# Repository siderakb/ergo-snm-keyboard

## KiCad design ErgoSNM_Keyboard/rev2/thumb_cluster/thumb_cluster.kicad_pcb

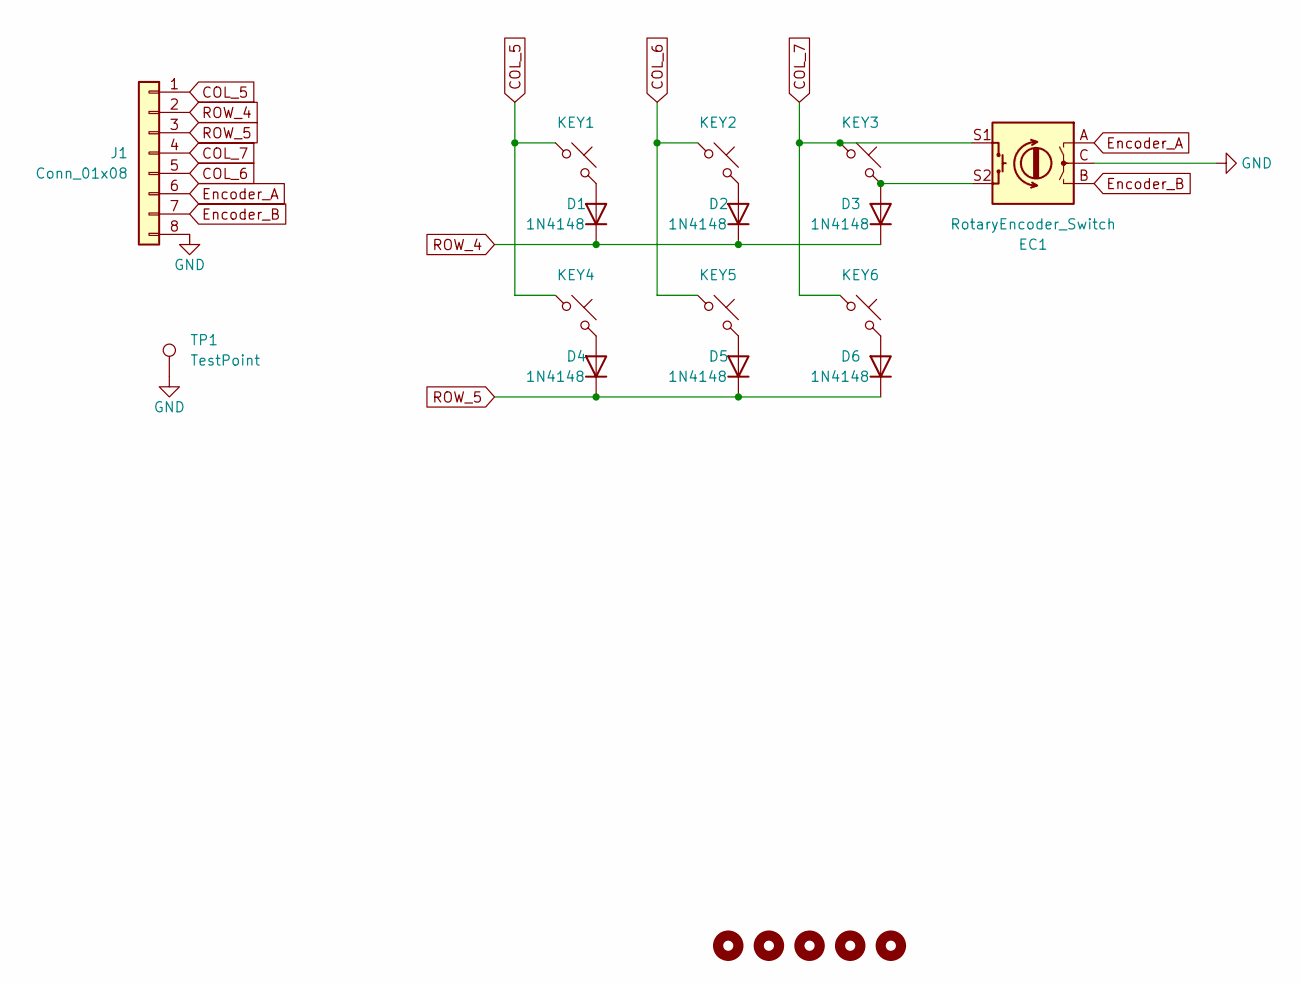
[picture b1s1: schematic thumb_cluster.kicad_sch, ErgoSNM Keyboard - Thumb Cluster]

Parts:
D1, D2, D3, D4, D5, D6: 1N4148; D_SOD-123; MFR. Part # 1N4148W; LCSC C81598
EC1: RotaryEncoder_Switch; RotaryEncoder_Alps_EC11E-Switch_Vertical_H20mm
H1, H2, H3, H4, H5: MountingHole; MountingHole_2.2mm_M2
J1: Conn_01x08; FPC_8P_0.5mm_AFC01-S08FCA-00; MFR. Part # SM08B-GHS-TB(LF)(SN); LCSC C265111
KEY1, KEY2, KEY3, KEY4, KEY5, KEY6: SW_Push_45deg; MX_switch_PTH_hotswap_A
TP1: TestPoint; TestPoint_Pad_D2.5mm

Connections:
COL_5: J1.1, KEY1.1, KEY4.1
COL_6: J1.5, KEY2.1, KEY5.1
COL_7: EC1.S1, J1.4, KEY3.1, KEY6.1
Encoder_A: EC1.A, J1.6
Encoder_B: EC1.B, J1.7
GND: EC1.C, J1.8, TP1.1
unnamed: D1.2 (A), KEY1.2
unnamed: D2.2 (A), KEY2.2
unnamed: D3.2 (A), EC1.S2, KEY3.2
unnamed: D4.2 (A), KEY4.2
unnamed: D5.2 (A), KEY5.2
unnamed: D6.2 (A), KEY6.2
ROW_4: D1.1 (K), D2.1 (K), D3.1 (K), J1.2
ROW_5: D4.1 (K), D5.1 (K), D6.1 (K), J1.3

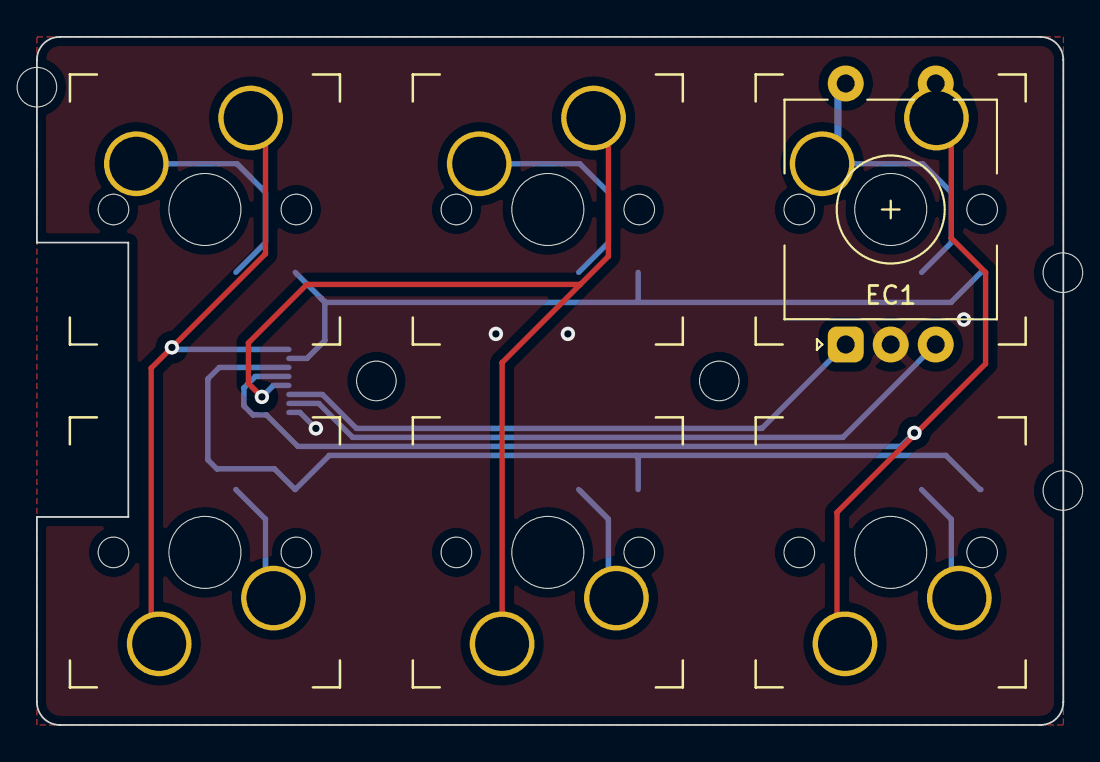
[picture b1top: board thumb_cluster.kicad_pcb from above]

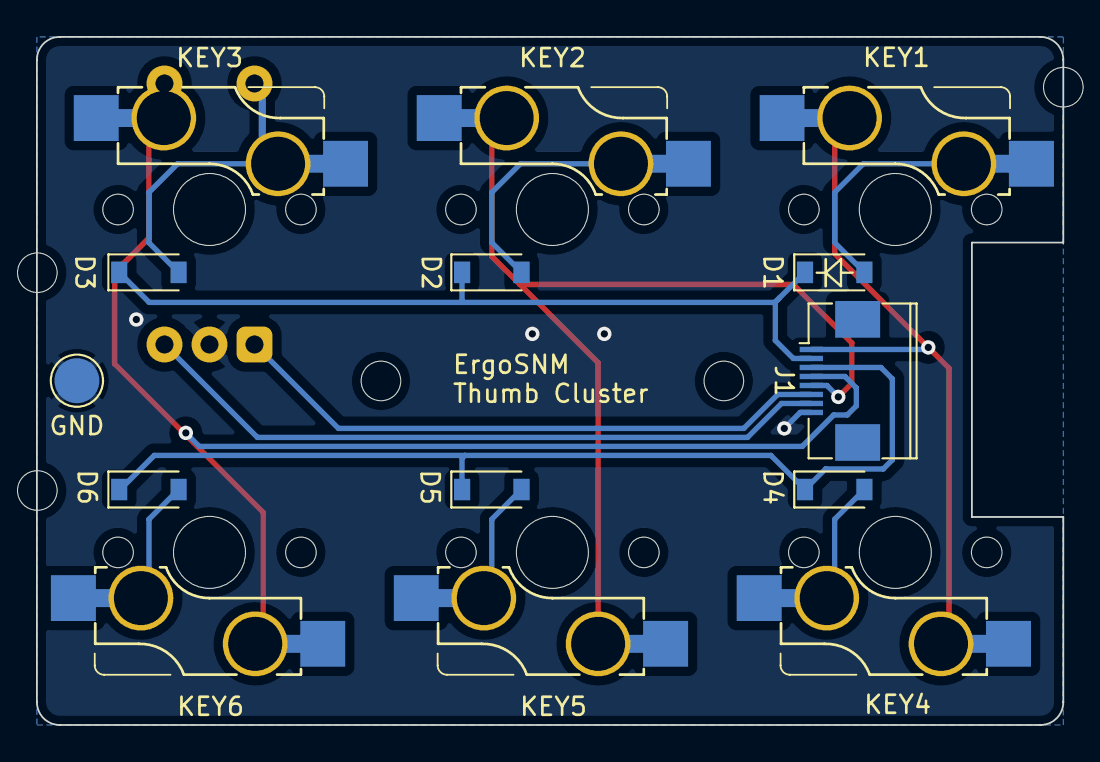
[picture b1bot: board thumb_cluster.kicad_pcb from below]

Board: 2 copper layers, 57.0 x 38.2 mm, 20 parts (8 on the bottom side), 14 nets.

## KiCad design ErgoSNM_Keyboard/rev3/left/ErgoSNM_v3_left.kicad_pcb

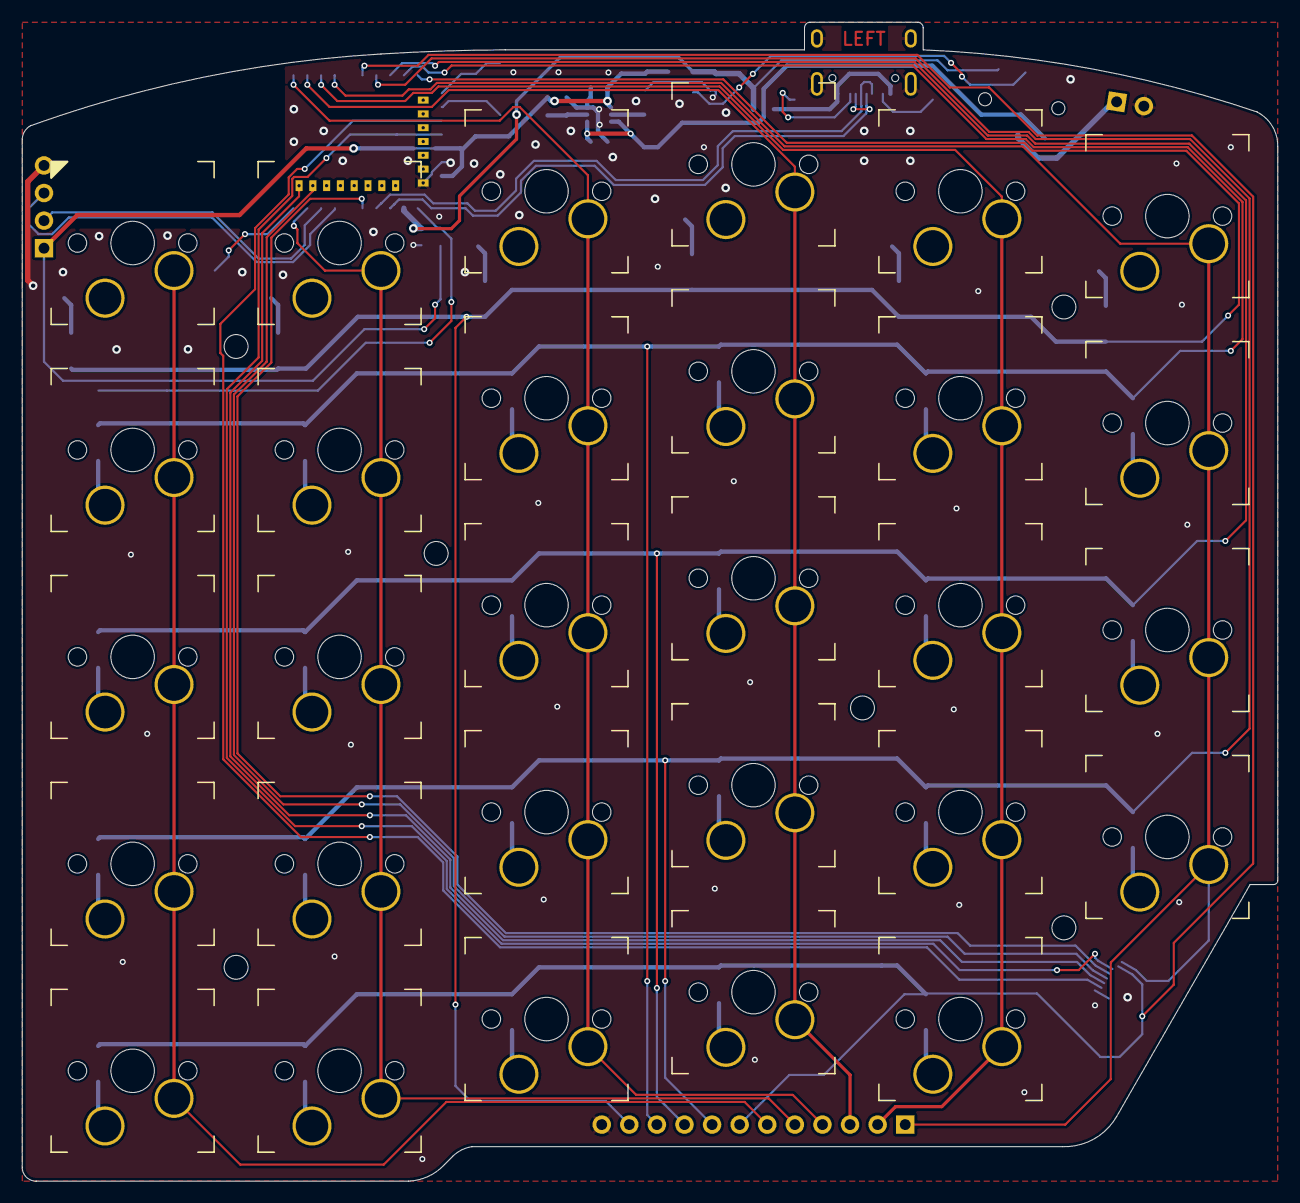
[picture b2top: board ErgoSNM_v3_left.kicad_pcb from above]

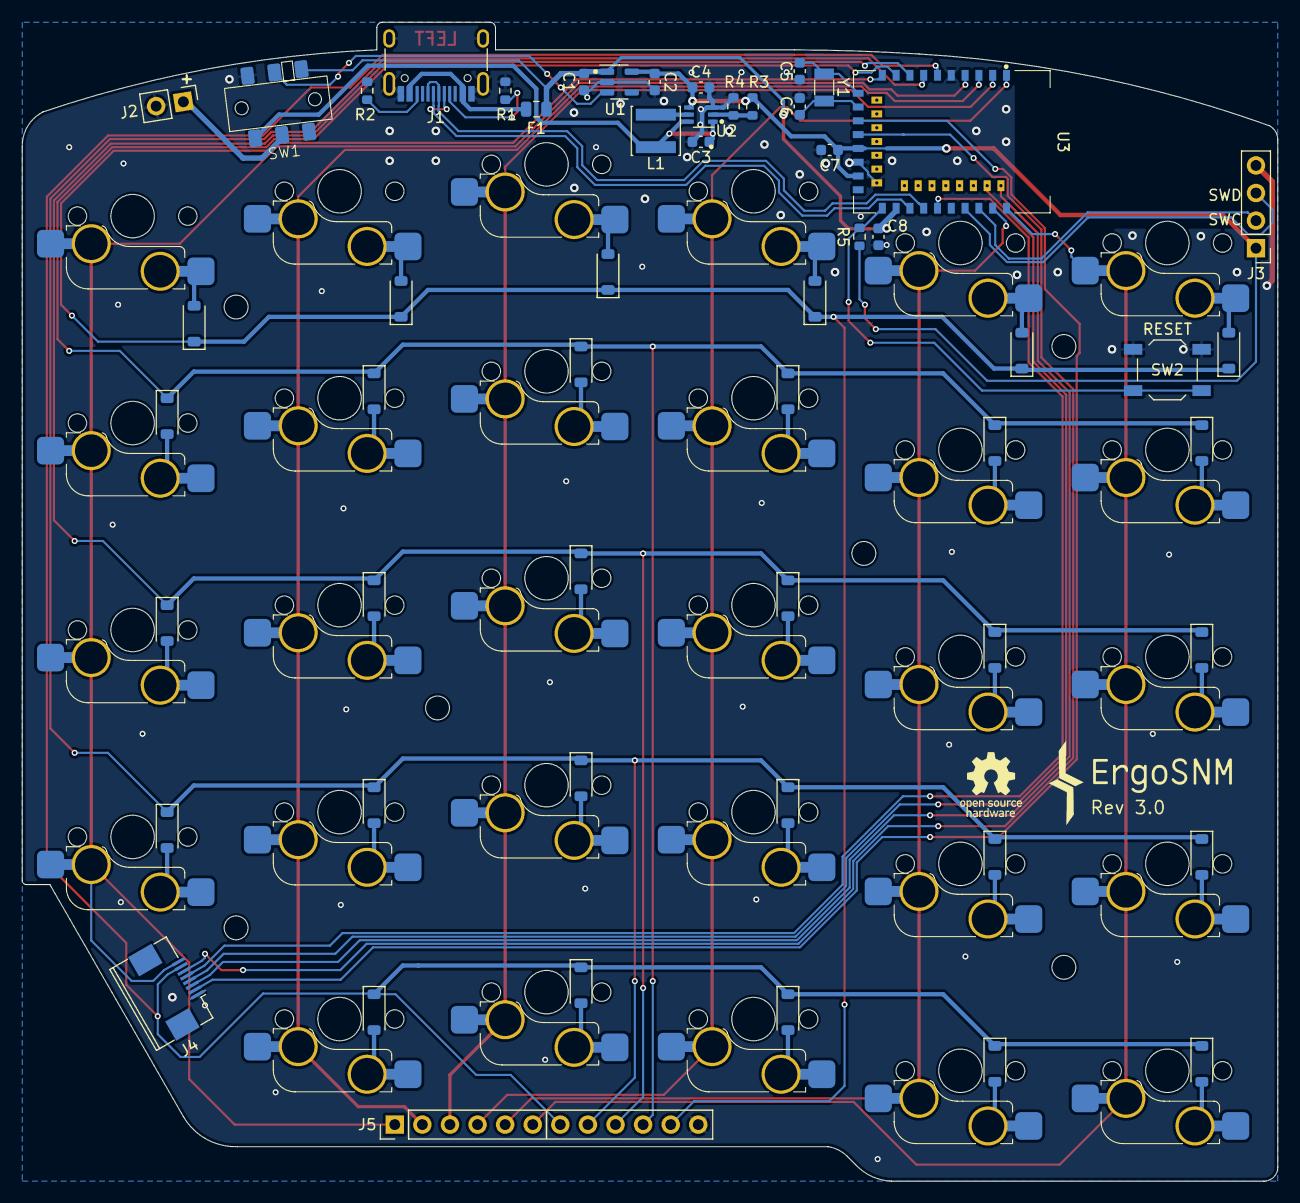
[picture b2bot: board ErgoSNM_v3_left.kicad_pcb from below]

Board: 2 copper layers, 115.6 x 106.7 mm, 90 parts (61 on the bottom side), 63 nets.

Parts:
C1, C2: 1uF; C_0603_1608Metric
C3, C4, C7, C8: 10uF; C_0603_1608Metric
C5, C6: 12pF; C_0603_1608Metric
D1, D2, D3, D4, D5, D6, D7, D8, D9, D10, D11, D12, D13, D14, D15, D16, D17, D18, D19, D20, D21, D22, D23, D24, D25, D26, D27, D28, D29: 1N4148; D_SOD-123
F1: 500mA, 6V; Fuse_0805_2012Metric
H1, H2, H3, H4, H5, H6: MountingHole; MountingHole_2.2mm_M2
J1: USB_C_Receptacle_USB2.0; USB_C_Receptacle_HRO_TYPE-C-31-M-12
J2: Conn_01x02; PinHeader_1x02_P2.54mm_Vertical
J3: Conn_01x04; PinHeader_1x04_P2.54mm_Vertical
J4: Conn_01x08; FPC_8P_0.5mm_AFC01-S08FCA-00
J5: Conn_01x12; PinHeader_1x12_P2.54mm_Vertical
KEY1, KEY2, KEY3, KEY4, KEY5, KEY6, KEY7, KEY8, KEY9, KEY10, KEY11, KEY12, KEY13, KEY14, KEY15, KEY16, KEY17, KEY18, KEY19, KEY20, KEY21, KEY22, KEY23, KEY24, KEY25, KEY26, KEY27, KEY28, KEY29: SW_Push_45deg; SW_MX_HotSwap_PTH
L1: 4.7uH; L_Changjiang_FNR4030S
R1, R2: 5.1k; R_0603_1608Metric
R3: 1.2M; R_0603_1608Metric
R4: 220k; R_0603_1608Metric
R5: 10k; R_0603_1608Metric
SW1: SW_DPDT_x2; MSKT-22D14-T
SW2: RESET; SW_SPST_TL3342
U1: RT9013-33GB; SOT-23-5
U2: TPS61220DCK; Texas_R-PDSO-G6
U3: E73-2G4M08S1C; E73-2G4M08S1C-52840
Y1: 32.768kHz; Crystal_SMD_3215-2Pin_3.2x1.5mm

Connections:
+5V: C1.1, C8.1, F1.2, SW1.4 (A), U1.1 (VIN), U3.27 (VBUS)
+BATT: C3.1, L1.1, SW1.3 (C), U2.1 (VIN), U2.6 (EN)
COL_0: J5.6, KEY1.2, KEY2.2, KEY3.2, KEY4.2, KEY5.2, U3.43 (P0.10/NFC2)
COL_1: J5.5, KEY6.2, KEY7.2, KEY8.2, KEY9.2, KEY10.2, U3.41 (P0.09/NFC1)
COL_2: J5.4, KEY11.2, KEY12.2, KEY13.2, KEY14.2, KEY15.2, U3.1 (P1.11)
COL_3: J5.3, KEY16.2, KEY17.2, KEY18.2, KEY19.2, KEY20.2, U3.2 (P1.10)
COL_4: J5.2, KEY21.2, KEY22.2, KEY23.2, KEY24.2, KEY25.2, U3.3 (P0.03)
COL_5: J4.8, J5.1, KEY26.2, KEY27.2, KEY28.2, KEY29.2, U3.4 (P0.28)
COL_6: J4.4, U3.40 (P1.04)
COL_7: J4.5, U3.33 (P0.13)
Encoder_A: J4.3, U3.42 (P1.06)
Encoder_B: J4.2, U3.15 (P0.05)
GND: C1.2, C2.2, C3.2, C4.2, C5.2, C6.1, C7.2, C8.2, J1.A1 (GND), J1.A12 (GND), J1.B1 (GND), J1.B12 (GND), J1.S1 (SHIELD), J2.2, J3.4, J4.1, J5.12, R1.2, R2.2, R4.2, SW1.6 (C), SW2.1, U1.2 (GND), U2.3 (GND), U3.5 (GND), U3.21 (GND), U3.24 (GND)
unnamed: D1.2 (A), KEY1.1
unnamed: D2.2 (A), KEY2.1
unnamed: D3.2 (A), KEY3.1
unnamed: D4.2 (A), KEY4.1
unnamed: D5.2 (A), KEY5.1
unnamed: D6.2 (A), KEY6.1
unnamed: D7.2 (A), KEY7.1
unnamed: D8.2 (A), KEY8.1
unnamed: D9.2 (A), KEY9.1
unnamed: D10.2 (A), KEY10.1
unnamed: D11.2 (A), KEY11.1
unnamed: D12.2 (A), KEY12.1
unnamed: D13.2 (A), KEY13.1
unnamed: D14.2 (A), KEY14.1
unnamed: D15.2 (A), KEY15.1
unnamed: D16.2 (A), KEY16.1
unnamed: D17.2 (A), KEY17.1
unnamed: D18.2 (A), KEY18.1
unnamed: D19.2 (A), KEY19.1
unnamed: D20.2 (A), KEY20.1
unnamed: D21.2 (A), KEY21.1
unnamed: D22.2 (A), KEY22.1
unnamed: D23.2 (A), KEY23.1
unnamed: D24.2 (A), KEY24.1
unnamed: D25.2 (A), KEY25.1
unnamed: D26.2 (A), KEY26.1
unnamed: D27.2 (A), KEY27.1
unnamed: D28.2 (A), KEY28.1
unnamed: D29.2 (A), KEY29.1
unnamed: J1.A5 (CC1), R1.1
unnamed: J1.B5 (CC2), R2.1
unnamed: J2.1, SW1.2 (B)
unnamed: SW1.5 (B), U1.3 (EN)
unnamed: R3.2, R4.1, U2.2 (FB)
unnamed: L1.2, U2.5 (L)
unnamed: C5.1, U3.11 (P0.00/XL1), Y1.2
unnamed: C6.2, U3.13 (P0.01/XL2), Y1.1
ROW_0: D1.1 (K), D6.1 (K), D11.1 (K), D16.1 (K), D21.1 (K), D26.1 (K), J5.11, U3.10 (P0.30)
ROW_1: D2.1 (K), D7.1 (K), D12.1 (K), D17.1 (K), D22.1 (K), D27.1 (K), J5.10, U3.9 (P0.31)
ROW_2: D3.1 (K), D8.1 (K), D13.1 (K), D18.1 (K), D23.1 (K), D28.1 (K), J5.9, U3.8 (P0.29)
ROW_3: D4.1 (K), D9.1 (K), D14.1 (K), D19.1 (K), D24.1 (K), D29.1 (K), J5.8, U3.7 (P0.02)
ROW_4: D5.1 (K), D10.1 (K), D15.1 (K), D20.1 (K), D25.1 (K), J4.7, J5.7, U3.6 (P1.13)
ROW_5: J4.6, U3.17 (P1.09)
SWC: J3.2, U3.39 (SWCLK)
SWD: J3.3, U3.37 (SWDIO)
USB_D+: J1.A6 (D+), J1.B6 (D+), U3.31 (D+)
USB_D-: J1.A7 (D-), J1.B7 (D-), U3.29 (D-)
VBUS: F1.1, J1.A4 (VBUS), J1.A9 (VBUS), J1.B4 (VBUS), J1.B9 (VBUS)
VDD: C2.1, C4.1, C7.1, J3.1, R3.1, R5.1, U1.5 (VOUT), U2.4 (VOUT), U3.19 (VDD), U3.23 (VDDH)
~RESET: R5.2, SW2.2, U3.26 (P0.18/RST)

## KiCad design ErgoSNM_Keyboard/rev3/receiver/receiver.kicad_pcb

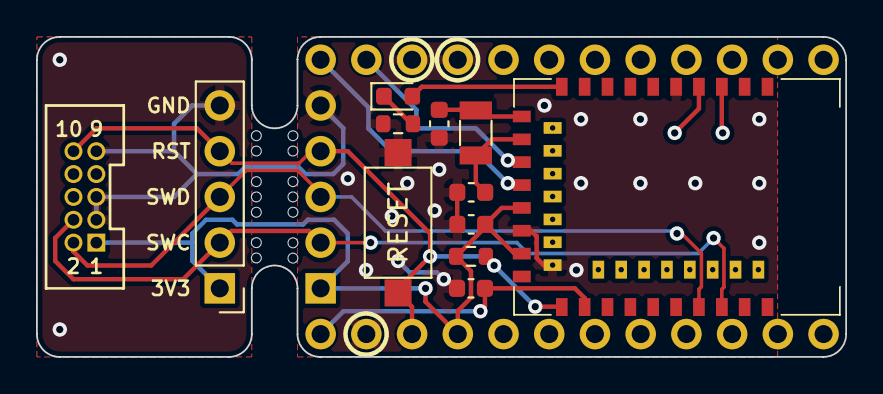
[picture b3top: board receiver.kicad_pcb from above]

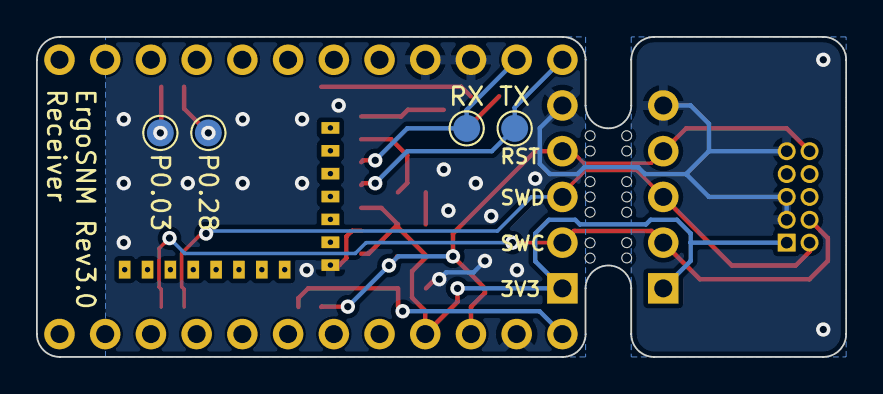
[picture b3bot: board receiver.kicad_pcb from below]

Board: 2 copper layers, 45.0 x 17.8 mm, 33 parts (6 on the bottom side), 14 nets.

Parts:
C1, C2: 12pF; C_0603_1608Metric
C3, C4: 10uF; C_0603_1608Metric
H1, H2, H3, H4, H5, H6, H7, H8, H9, H10, H11, H12, H13, H14: MountingHole; Mouse bite
J1: Conn_02x05_Counter_Clockwise; PinHeader_2x05_P1.27mm_Vertical
J2, J4: Conn_01x13; PinHeader_1x12_P2.54mm_Vertical
J3, J5: Conn_01x04; PinHeader_1x05_P2.54mm_Vertical
LD1: Red; LED_0603_1608Metric
R1: 10k; R_0603_1608Metric
R2: 1k; R_0603_1608Metric
SW1: RESET; SW_SPST_CK_RS282G05A3
TP1, TP2, TP3, TP4: TestPoint; TestPoint_Pad_D1.5mm
U1: E73-2G4M08S1C; E73-2G4M08S1C-52840
Y1: 32.768kHz; Crystal_SMD_3215-2Pin_3.2x1.5mm

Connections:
+3.3V: C3.1, J1.1, J3.1, J4.4, J5.1, R1.1, U1.19 (VDD), U1.23 (VDDH)
+5V: C4.1, J4.1, U1.27 (VBUS)
GND: C1.2, C2.1, C3.2, C4.2, J1.3, J1.5, J1.9, J2.3, J2.4, J3.5, J4.2, J5.5, R2.2, SW1.1, U1.5 (GND), U1.21 (GND), U1.24 (GND)
LED: LD1.2 (A), U1.10 (P0.30)
unnamed: LD1.1 (K), R2.1
unnamed: C1.1, U1.11 (P0.00/XL1), Y1.2
unnamed: C2.2, U1.13 (P0.01/XL2), Y1.1
unnamed: TP1.1, U1.3 (P0.03)
unnamed: TP2.1, U1.4 (P0.28)
RX: J2.2, TP4.1, U1.15 (P0.05)
SWC: J1.4, J3.2, J5.2, U1.39 (SWCLK)
SWD: J1.2, J3.3, J5.3, U1.37 (SWDIO)
TX: J2.1, TP3.1, U1.17 (P1.09)
~RESET: J1.10, J3.4, J4.3, J5.4, R1.2, SW1.2, U1.26 (P0.18/RST)

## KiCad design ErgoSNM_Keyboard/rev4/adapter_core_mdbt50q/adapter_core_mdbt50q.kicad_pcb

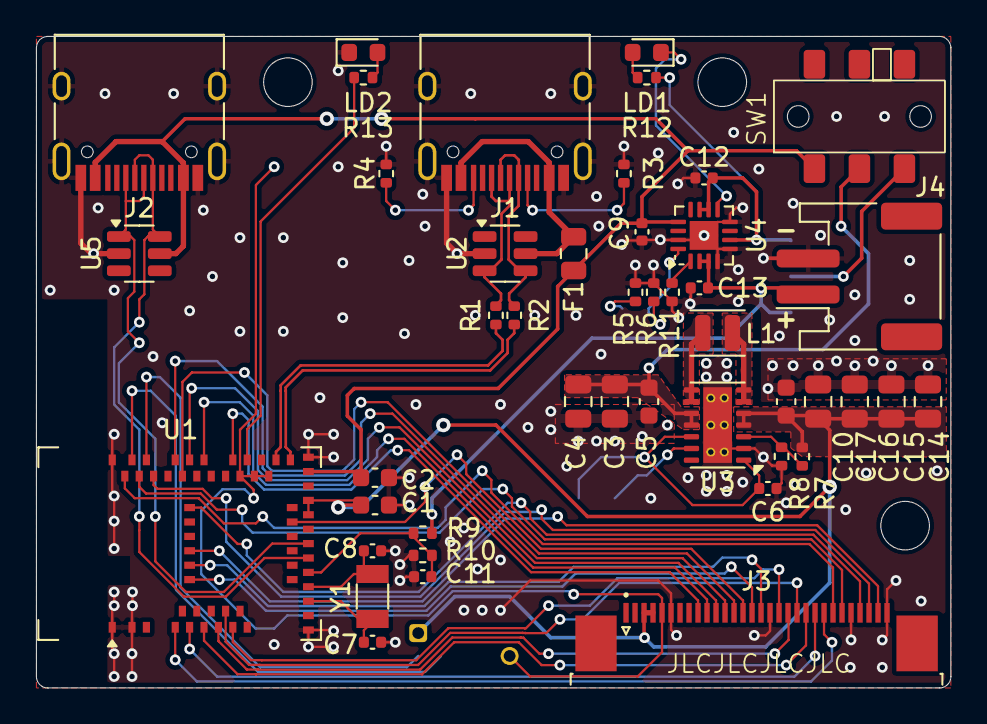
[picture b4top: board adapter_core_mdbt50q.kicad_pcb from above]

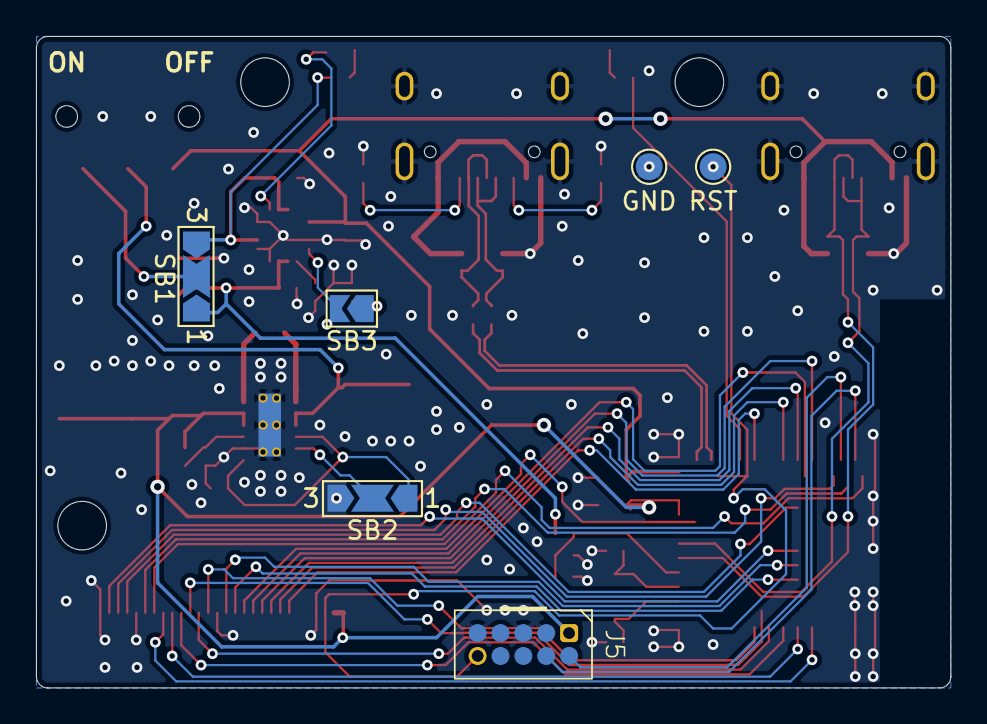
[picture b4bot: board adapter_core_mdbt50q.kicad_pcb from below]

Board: 2 copper layers, 50.8 x 36.2 mm, 54 parts (6 on the bottom side), 53 nets.

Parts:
C1, C2: 10uF; C_0603_1608Metric
C3, C4, C14, C15, C16, C17: 22uF; C_0805_2012Metric
C5, C10: 2.2uF; C_0603_1608Metric
C6, C11: 100nF; C_0402_1005Metric
C7, C8: 12pF; C_0402_1005Metric
C9: 1uF; C_0402_1005Metric
C12, C13: 4.7uF; C_0402_1005Metric
F1: 500mA, 6V; Fuse_0805_2012Metric
H1, H2, H3: MountingHole; MountingHole_2.7mm_M2.5_ISO7380
J1, J2: USB_C_Receptacle_USB2.0; USB_C_Receptacle_HRO_TYPE-C-31-M-12
J3: Conn_01x30; TE_3-1734839-0_1x30-1MP_P0.5mm_Horizontal
J4: Conn_Batt; JST_PH_S2B-PH-SM4-TB_1x02-1MP_P2.00mm_Horizontal
J5: Debug; SWD 10pin
L1: 1.5uH; L_Changjiang_FNR252012S
LD1: RED; LED_0603_1608Metric
LD2: BLUE; LED_0603_1608Metric
R1, R2: 27R; R_0402_1005Metric
R3, R4: 5.1k; R_0402_1005Metric
R5: 2k; R_0402_1005Metric
R6, R11, R12, R13: 10k; R_0402_1005Metric
R7: 1M; R_0402_1005Metric
R8: 180k; R_0402_1005Metric
R9: 820k; R_0402_1005Metric
R10: 2M; R_0402_1005Metric
SB1: Vsrc Select; SolderJumper-3_P2.0mm_Open_TrianglePad1.0x1.5mm_NumberLabels
SB2: Power Save; SolderJumper-3_P2.0mm_Open_TrianglePad1.0x1.5mm_NumberLabels
SB3: Charge Boost; SolderJumper-2_P1.3mm_Open_TrianglePad1.0x1.5mm
SW1: SW_DPDT_x2; MSKT-22D14-T
TP1: RST; TestPoint_Pad_D1.5mm
TP2: GND; TestPoint_Pad_D1.5mm
U1: MDBT50Q-1MV2; Raytac_MDBT50Q
U2, U5: SRV05-4; SOT-23-6
U3: TPS63020; VSON-14-1EP_3x4.45mm_P0.65mm_EP1.6x4.2mm_ThermalVias
U4: BQ24075RGT; VQFN-16-1EP_3x3mm_P0.5mm_EP1.6x1.6mm
Y1: 32.768kHz; Crystal_SMD_3215-2Pin_3.2x1.5mm

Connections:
+5V: F1.1, J1.A4 (VBUS), J1.A9 (VBUS), J1.B4 (VBUS), J1.B9 (VBUS), U2.5 (VP)
+BATT: C13.2, J4.1, R9.1, SB1.1 (A), U4.2 (BAT), U4.3 (BAT)
/MCU_D+: R2.2, U1.35 (D+)
/MCU_D-: R1.1, U1.34 (D-)
/PWR_SAVE: SB2.2 (C), U3.13 (PS/SYNC)
/VINA: C6.1, SB2.1 (A), U3.1 (VINA), U3.12 (EN)
GND: C1.2, C2.1, C3.2, C4.2, C5.2, C6.2, C7.1, C8.1, C9.2, C10.2, C11.2, C12.1, C13.1, C14.2, C15.2, C16.2, C17.2, J1.A1 (GND), J1.A12 (GND), J1.B1 (GND), J1.B12 (GND), J1.S1 (SHIELD), J2.A1 (GND), J2.A12 (GND), J2.B1 (GND), J2.B12 (GND), J2.S1 (SHIELD), J3.6, J3.17, J3.26, J3.30, J4.2, J5.3, J5.5, J5.9, LD2.1 (K), R3.2, R4.2, R5.2, R6.2, R8.2, R10.2, R11.1, SB2.3 (B), TP2.1, U1.1 (GND), U1.2 (GND), U1.15 (GND), U1.33 (GND), U1.55 (GND), U2.2 (VN), U3.2 (GND), U3.15 (PAD), U4.4 (~CE), U4.5 (EN2), U4.8 (VSS), U4.15 (SYSOFF), U4.17 (VSS), U5.2 (VN)
unnamed: J1.A5 (CC1), R3.1
unnamed: J1.B5 (CC2), R4.1
unnamed: L1.1, U3.8 (L1), U3.9 (L1)
unnamed: L1.2, U3.6 (L2), U3.7 (L2)
unnamed: LD1.2 (A), R12.2
unnamed: LD1.1 (K), U4.9 (~CHG)
unnamed: LD2.2 (A), R13.2
unnamed: SB1.2 (C), SW1.1 (A)
unnamed: R5.1, SB3.1 (A)
unnamed: R6.1, SB3.2 (B), U4.16 (ISET)
unnamed: C3.1, C4.1, C5.1, SW1.2 (B), U3.10 (VIN), U3.11 (VIN)
unnamed: R7.2, R8.1, U3.3 (FB)
unnamed: R11.2, U4.1 (TS)
P0.02: J3.20, U1.11 (P0.02)
P0.04: C11.1, R9.2, R10.1, U1.20 (P0.04)
P0.06: J2.A7 (D-), J2.B7 (D-), U1.22 (P0.06), U5.6 (IO4)
P0.08: J2.A6 (D+), J2.B6 (D+), U1.24 (P0.08), U5.1 (IO1)
P0.09: J3.25, U1.52 (P0.09)
P0.10: J3.24, U1.54 (P0.10)
P0.11: J3.14, U1.27 (P0.11)
P0.15: R13.1, U1.39 (P0.15)
P0.17: J3.9, U1.41 (P0.17)
P0.20: J3.10, U1.44 (P0.20)
P0.22: J3.11, U1.46 (P0.22)
P0.24: J3.12, U1.48 (P0.24)
P0.29: J3.19, U1.10 (P0.29)
P0.31: J3.18, U1.12 (P0.31)
P1.00: J3.13, U1.47 (P1.00)
P1.01: J3.27, U1.61 (P1.01)
P1.02: J3.28, U1.50 (P1.02)
P1.04: J3.15, U1.56 (P1.04)
P1.06: J3.16, U1.57 (P1.06)
P1.07: J3.29, U1.58 (P1.07)
P1.11: J3.23, U1.4 (P1.11)
P1.13: J3.22, U1.6 (P1.13)
P1.15: J3.21, U1.8 (P1.15)
RESET: J3.5, J5.10, TP1.1, U1.36 (P0.14), U1.38 (P0.16), U1.40 (P0.18)
SWC: J5.4, U1.53 (SWDCLK)
SWD: J5.2, U1.51 (SWDIO)
USB_D+: J1.A6 (D+), J1.B6 (D+), R2.1, U2.3 (IO2)
USB_D-: J1.A7 (D-), J1.B7 (D-), R1.2, U2.4 (IO3)
VBUS: C2.2, C9.1, F1.2, J2.A4 (VBUS), J2.A9 (VBUS), J2.B4 (VBUS), J2.B9 (VBUS), SW1.3 (C), U1.32 (VBUS), U4.13 (IN), U5.5 (VP)
VDD: C1.1, C10.1, C14.1, C15.1, C16.1, C17.1, J3.3, J3.4, J5.1, R7.1, U1.28 (VDD), U1.30 (VDDH), U3.4 (VOUT), U3.5 (VOUT)
VDDH: C12.2, R12.1, SB1.3 (B), U4.6 (EN1), U4.10 (OUT), U4.11 (OUT)
XL1: C7.2, U1.17 (P0.00), Y1.2
XL2: C8.2, U1.18 (P0.01), Y1.1

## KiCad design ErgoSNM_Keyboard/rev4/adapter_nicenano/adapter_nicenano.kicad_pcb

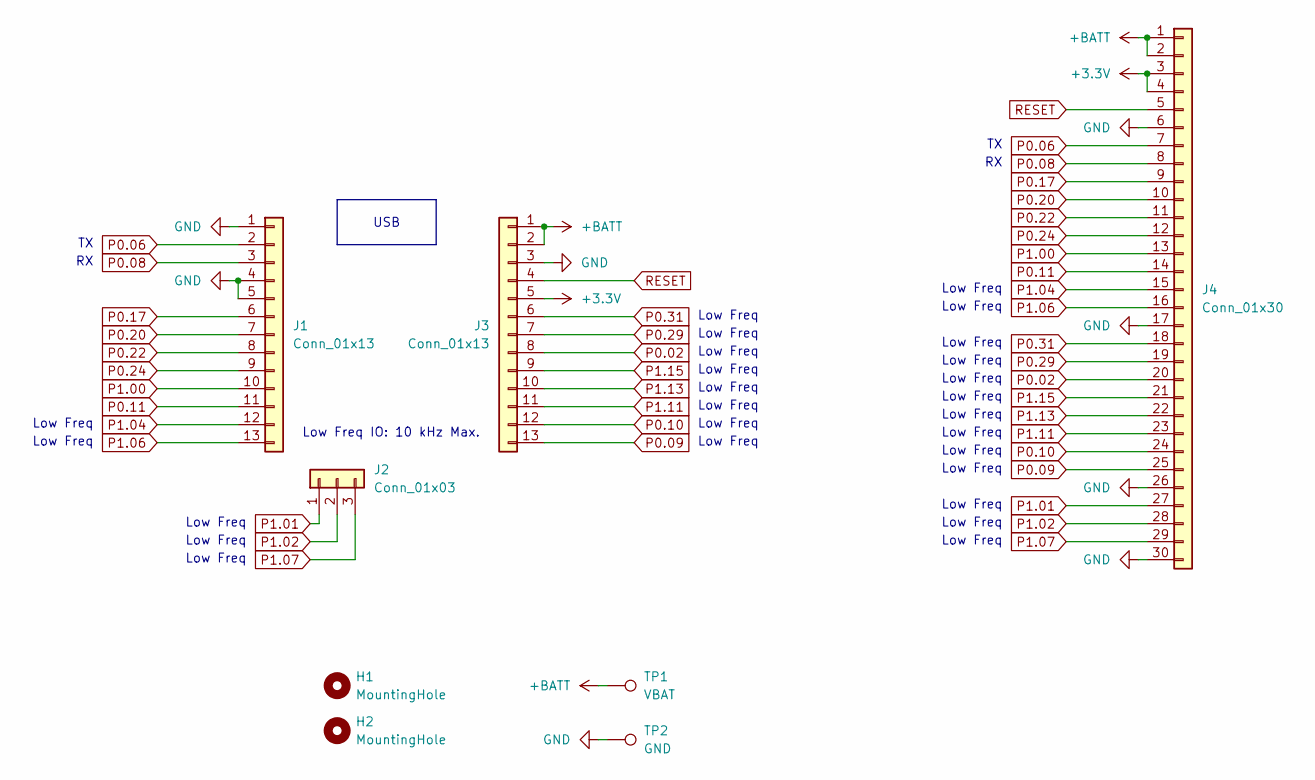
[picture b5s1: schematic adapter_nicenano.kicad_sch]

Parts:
H1, H2: MountingHole; MountingHole_2.7mm_M2.5_ISO7380
J1, J3: Conn_01x13; PinHeader_1x13_P2.54mm_Vertical
J2: Conn_01x03; PinHeader_1x03_P2.54mm_Vertical
J4: Conn_01x30; TE_3-1734839-0_1x30-1MP_P0.5mm_Horizontal
TP1: VBAT; TestPoint_Keystone_5015_Micro_Mini
TP2: GND; TestPoint_Keystone_5015_Micro_Mini

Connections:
+3.3V: J3.5, J4.3, J4.4
+BATT: J3.1, J3.2, J4.1, J4.2, TP1.1
GND: J1.1, J1.4, J1.5, J3.3, J4.6, J4.17, J4.26, J4.30, TP2.1
P0.02: J3.8, J4.20
P0.06: J1.2, J4.7
P0.08: J1.3, J4.8
P0.09: J3.13, J4.25
P0.10: J3.12, J4.24
P0.11: J1.11, J4.14
P0.17: J1.6, J4.9
P0.20: J1.7, J4.10
P0.22: J1.8, J4.11
P0.24: J1.9, J4.12
P0.29: J3.7, J4.19
P0.31: J3.6, J4.18
P1.00: J1.10, J4.13
P1.01: J2.1, J4.27
P1.02: J2.2, J4.28
P1.04: J1.12, J4.15
P1.06: J1.13, J4.16
P1.07: J2.3, J4.29
P1.11: J3.11, J4.23
P1.13: J3.10, J4.22
P1.15: J3.9, J4.21
RESET: J3.4, J4.5

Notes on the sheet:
Low Freq
Low Freq IO: 10 kHz Max.
USB

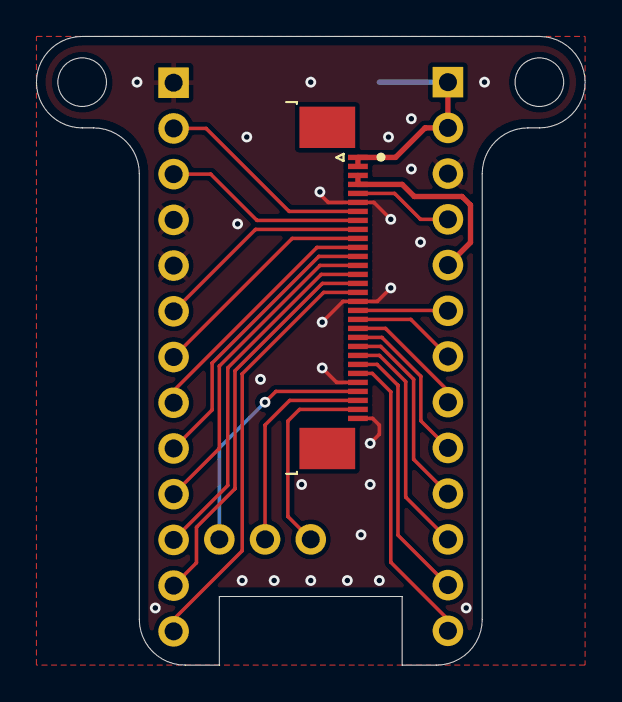
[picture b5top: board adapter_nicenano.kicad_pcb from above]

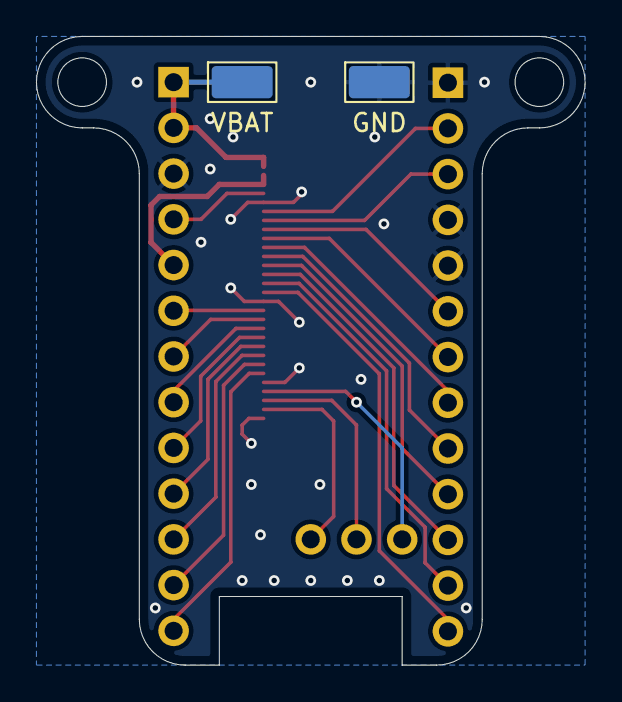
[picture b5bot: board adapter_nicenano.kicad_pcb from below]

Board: 2 copper layers, 30.5 x 34.9 mm, 8 parts (2 on the bottom side), 25 nets.

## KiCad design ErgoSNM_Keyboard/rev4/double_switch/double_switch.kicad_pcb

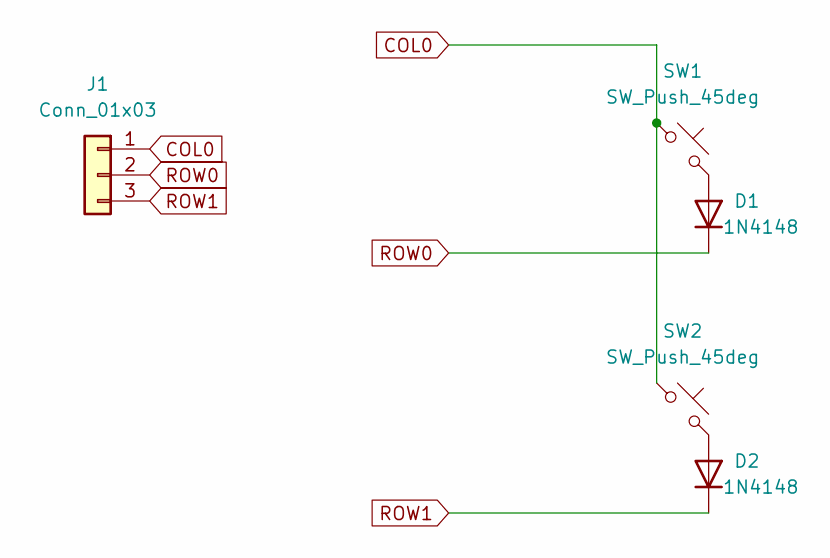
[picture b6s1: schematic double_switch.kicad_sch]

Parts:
D1, D2: 1N4148; D_SOD-123; MFR. Part # 1N4148W; JLCPCB Part # C81598
J1: Conn_01x03; PinHeader_1x03_P2.54mm_Vertical
SW1, SW2: SW_Push_45deg; SW_MX_Kailh_Choc_V1V2_HotSwap_Hybrid_alt1

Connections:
COL0: J1.1, SW1.1, SW2.1
unnamed: D1.2 (A), SW1.2
unnamed: D2.2 (A), SW2.2
ROW0: D1.1 (K), J1.2
ROW1: D2.1 (K), J1.3

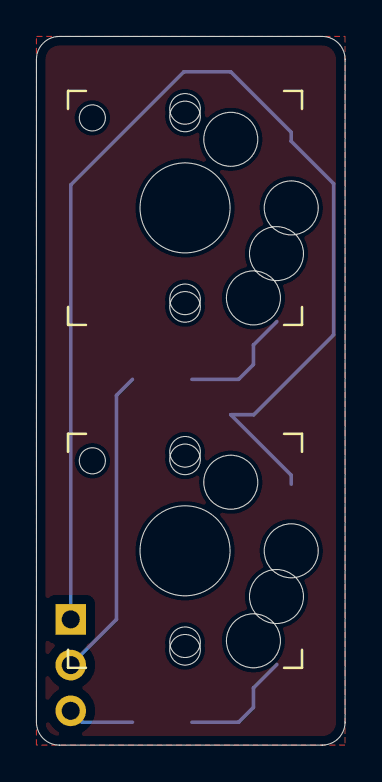
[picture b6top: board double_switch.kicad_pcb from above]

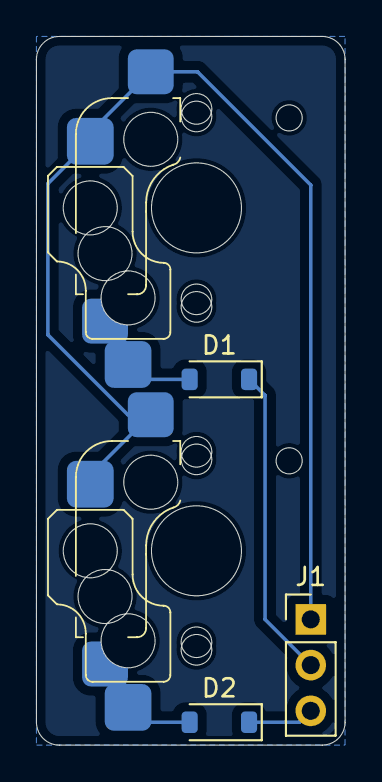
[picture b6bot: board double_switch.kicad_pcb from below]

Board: 2 copper layers, 17.1 x 39.4 mm, 5 parts (3 on the bottom side), 5 nets.

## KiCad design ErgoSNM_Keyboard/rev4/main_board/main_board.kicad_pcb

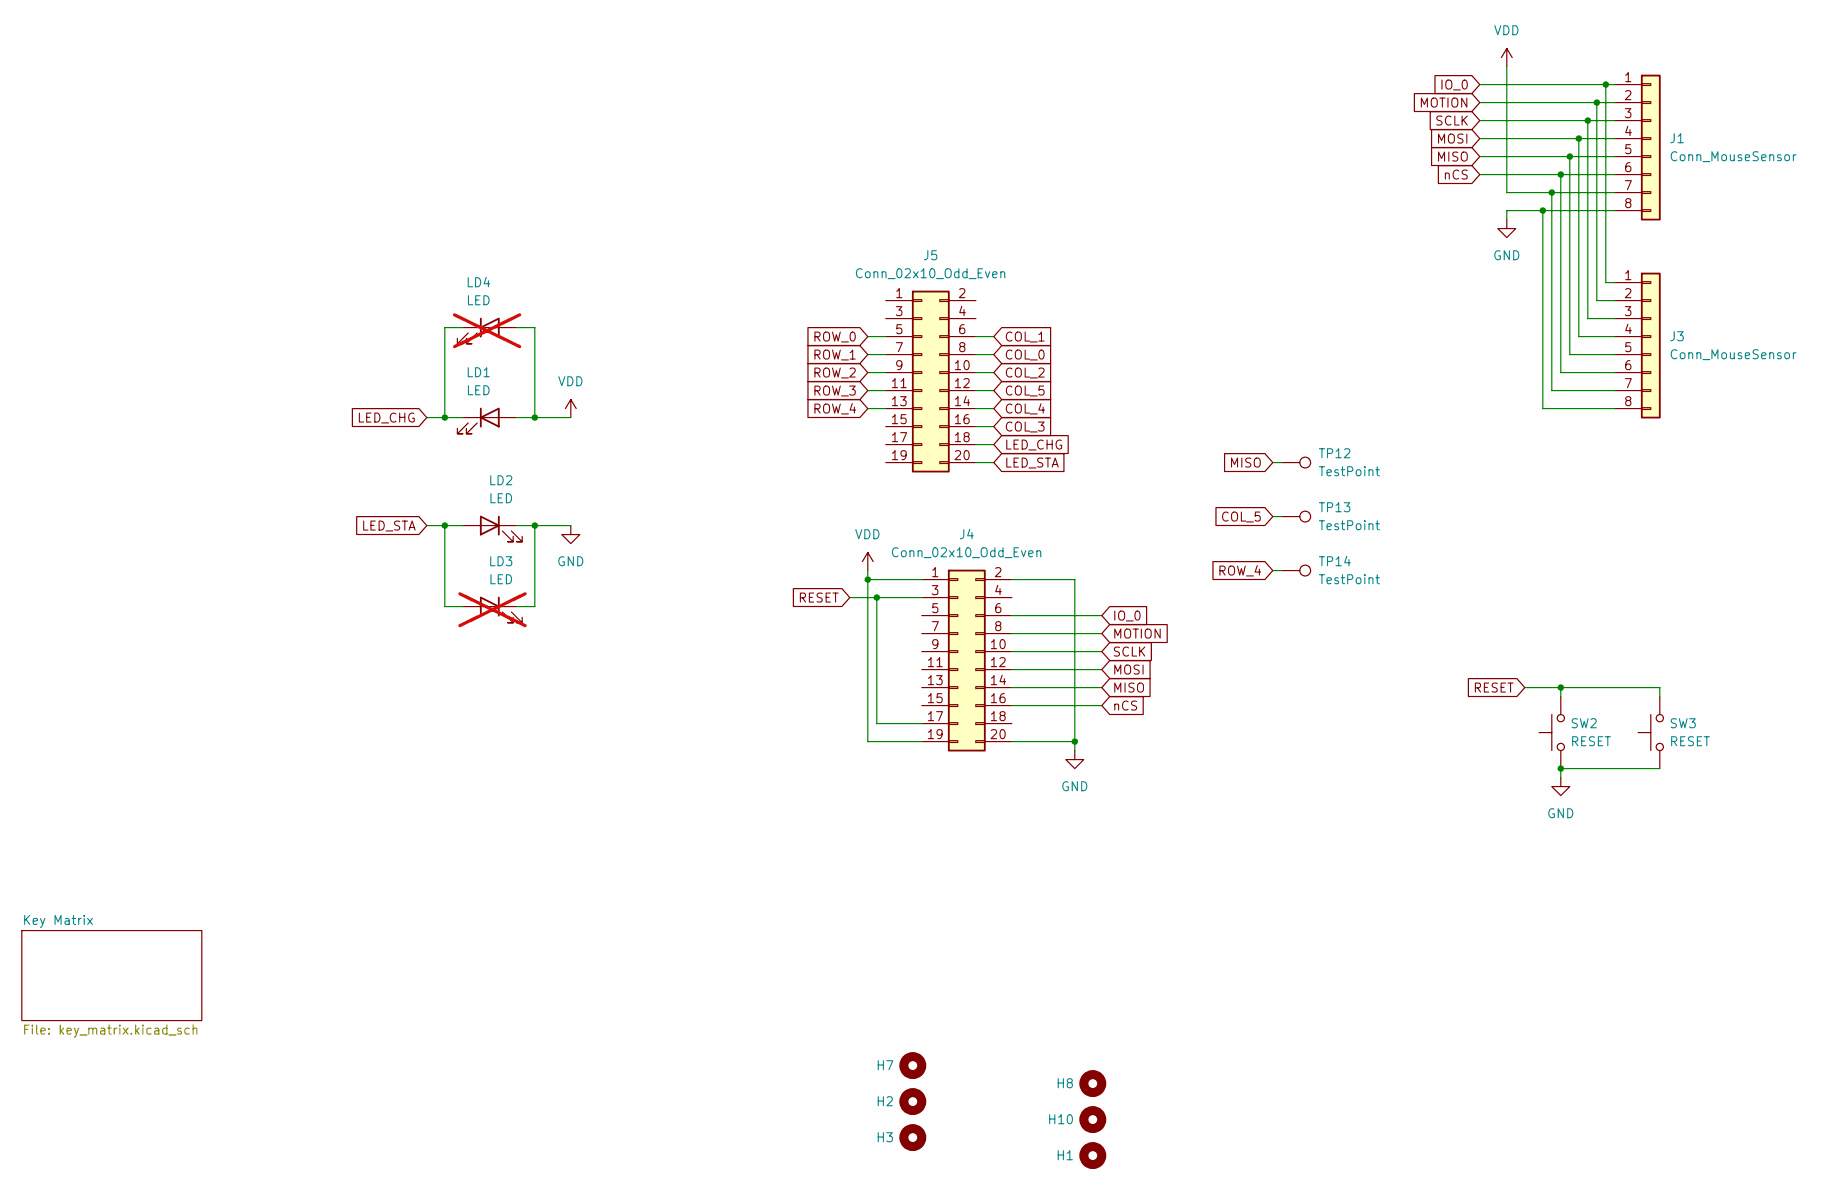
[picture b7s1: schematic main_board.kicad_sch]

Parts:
H1, H8, H10: MountingHole_2.7mm_M2.5_ISO14580
H2, H3, H7: mounting_hole_6.5mm
J1, J3: Conn_MouseSensor; FPC_8P_0.5mm_AFC01-S08FCA-00; MFR. Part # FPC-05F-8PH20; JLCPCB Part # C2856797
J4, J5: Conn_02x10_Odd_Even; PinSocket_2x10_P1.27mm_Vertical
LD1, LD2: LED; LED_0603_1608Metric_Pad1.05x0.95mm_HandSolder
LD3, LD4: LED; LED_0603_1608Metric_Pad1.05x0.95mm_HandSolder; not fitted
SW2, SW3: RESET; SW_SPST_TL3342; MFR. Part # TS-1187A-B-A-B; JLCPCB Part # C318884
TP12, TP13, TP14: TestPoint; TestPoint_Pad_1.5x1.5mm

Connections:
COL_0: J5.8; also elsewhere on the board
COL_1: J5.6; also elsewhere on the board
COL_2: J5.10; also elsewhere on the board
COL_3: J5.16; also elsewhere on the board
COL_4: J5.14; also elsewhere on the board
COL_5: J5.12, TP13.1; also elsewhere on the board
GND: J1.8, J3.8, J4.2, J4.20, LD2.1 (K), LD3.1 (K), SW2.1, SW3.1
IO_0: J1.1, J3.1, J4.6
LED_CHG: J5.18, LD1.1 (K), LD4.1 (K)
LED_STA: J5.20, LD2.2 (A), LD3.2 (A)
MISO: J1.5, J3.5, J4.14, TP12.1
MOSI: J1.4, J3.4, J4.12
MOTION: J1.2, J3.2, J4.8
RESET: J4.3, J4.17, SW2.2, SW3.2
ROW_0: J5.5; also elsewhere on the board
ROW_1: J5.7; also elsewhere on the board
ROW_2: J5.9; also elsewhere on the board
ROW_3: J5.11; also elsewhere on the board
ROW_4: J5.13, TP14.1; also elsewhere on the board
SCLK: J1.3, J3.3, J4.10
VDD: J1.7, J3.7, J4.1, J4.19, LD1.2 (A), LD4.2 (A)
nCS: J1.6, J3.6, J4.16

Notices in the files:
ErgoSNM_Keyboard/rev2/thumb_cluster/thumb_cluster.kicad_pcb:
MIT License
ErgoSNM_Keyboard/rev3/left/ErgoSNM_v3_left.kicad_pcb:
Open source hardware, CERN-OHL-P v2
